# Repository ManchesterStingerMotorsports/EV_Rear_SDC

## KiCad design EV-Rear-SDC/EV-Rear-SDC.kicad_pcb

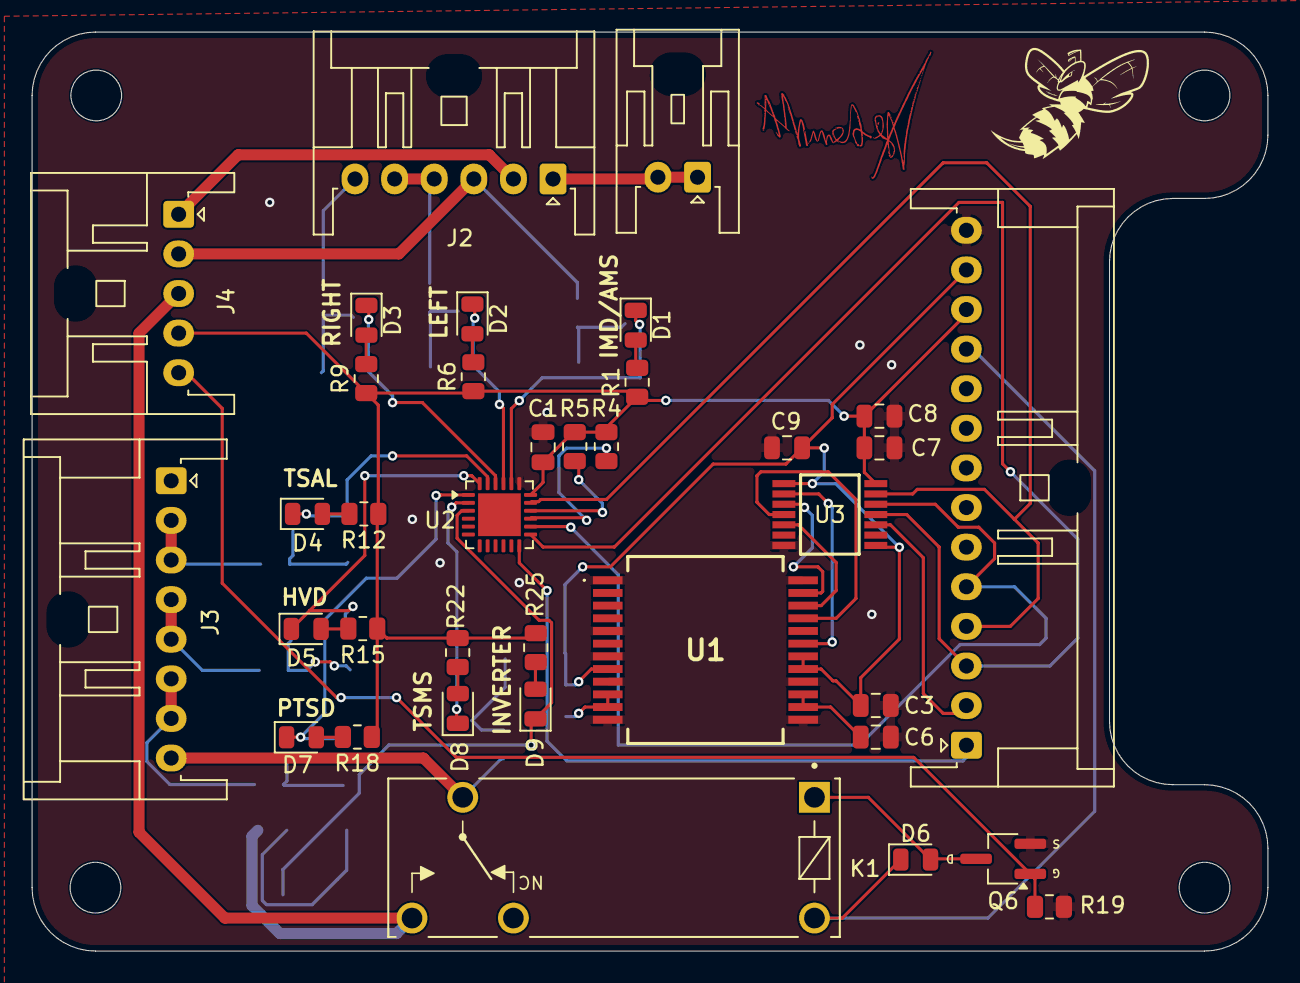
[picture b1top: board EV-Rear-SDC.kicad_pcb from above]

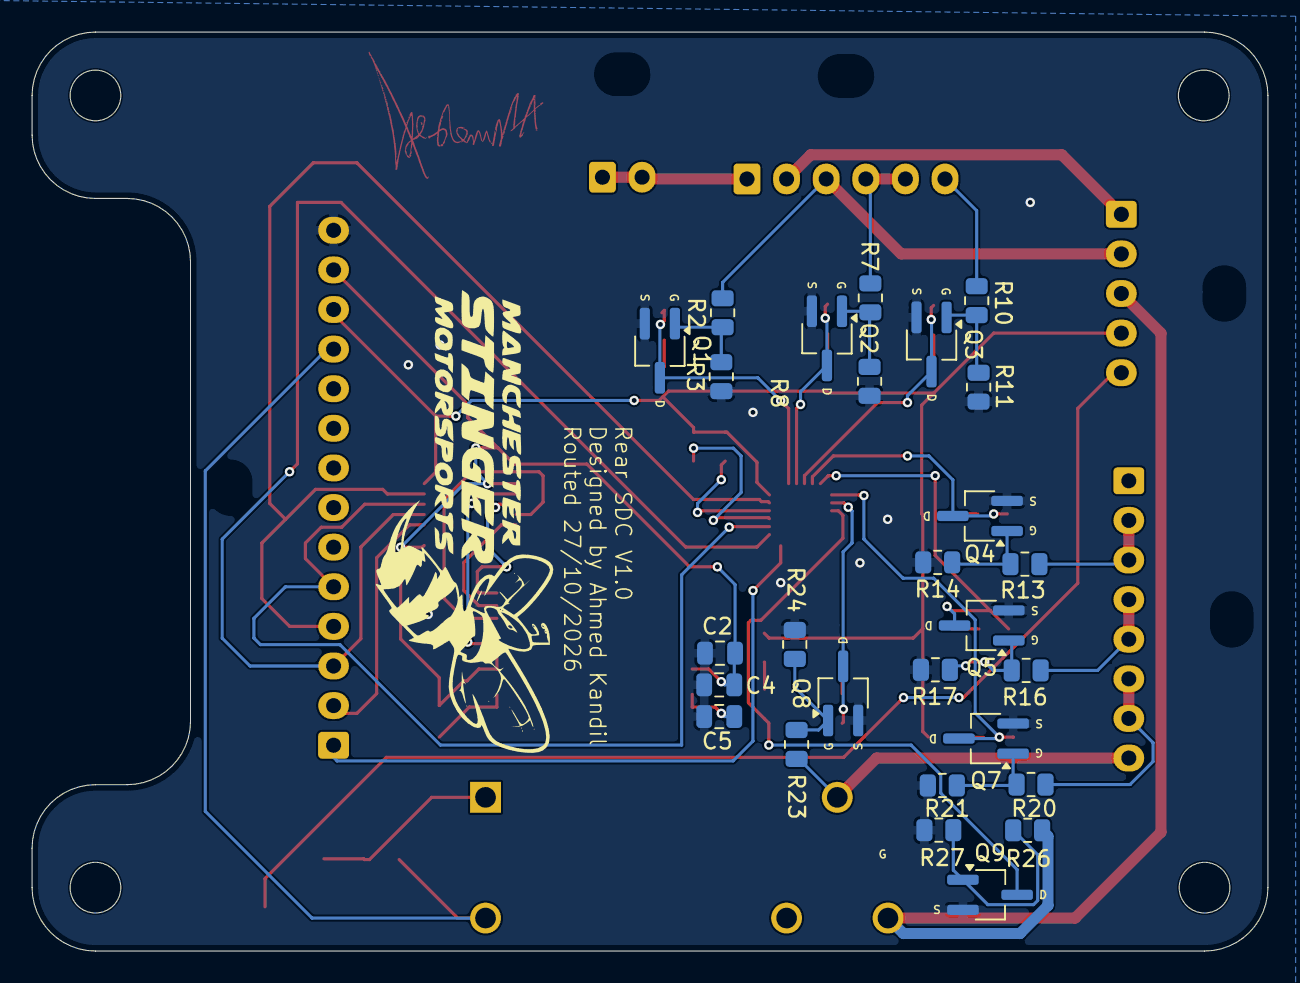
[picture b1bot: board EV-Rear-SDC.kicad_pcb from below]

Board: 2 copper layers, 78.0 x 58.0 mm, 63 parts (27 on the bottom side), 53 nets.

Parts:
C1, C2, C3, C7, C9: 0.1u; C_0805_2012Metric
C4, C6, C8: 1u; C_0805_2012Metric
C5: 10u; C_0805_2012Metric
D1, D2, D3, D4, D5, D7, D8, D9: LED; LED_0805_2012Metric
D6: D; D_0805_2012Metric
J1: JST-XA; JST_XA_S02B-XASK-1_1x02_P2.50mm_Horizontal
J2: Conn_01x06; JST_XA_S06B-XASK-1_1x06_P2.50mm_Horizontal
J3: Conn_01x08; JST_XA_S08B-XASK-1_1x08_P2.50mm_Horizontal
J4: Conn_01x05; JST_XA_S05B-XASK-1_1x05_P2.50mm_Horizontal
J5: Conn_01x14; JST_XA_S14B-XASK-1_1x14_P2.50mm_Horizontal
K1: Relay_SPDT_G6RN
Q1, Q2, Q3, Q4, Q5, Q6, Q7, Q8, Q9: BSS205N; MOSFET_Single_SOT-23
R1, R6, R9, R12, R15, R18, R22, R25: 300R; R_0805_2012Metric
R2, R7, R10, R13, R16, R20, R23, R26: 75K; R_0805_2012Metric
R3, R8, R11, R14, R17, R21, R24, R27: 25k; R_0805_2012Metric
R4, R5: 10k; R_0805_2012Metric
R19: 100k; R_0805_2012Metric
U1: SCH16T-K01-10; SCH16TK0110
U2: QFN-24-1EP_4x4mm_P0.5mm_EP2.7x2.7mm
U3: MAX3390EEUD_T; SOP65P640X110-14N

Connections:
5V_CS_C: J5.1, U2.12 (CS)
5V_CS_D: J5.2, U3.10 (O_VCC4)
5V_MISO: J5.4, U2.17 (SDO), U3.13 (I_VCC1)
5V_MOSI: J5.5, U2.14 (SDI), U3.12 (O_VCC2)
5V_SCLK: J5.3, U2.13 (SCLK), U3.11 (O_VCC3)
+3V3: C2.1, C3.1, C4.1, C9.1, J5.13, U1.8 (V3P3_1), U1.17 (V3P3_2), U1.18 (VDDIO), U3.1 (VL), U3.8 (~THREE-STATE)
+24V: D6.1 (K), J5.11, K1.5
BSPD: J2.2, J4.1
CS_D: U1.22 (CS), U3.5 (I_VL4)
GND: C1.2, C2.2, C3.2, C4.2, C5.2, C6.2, C7.2, C8.2, C9.2, J5.14, Q1.2 (S), Q2.2 (S), Q3.2 (S), Q4.2 (S), Q5.2 (S), Q6.2 (S), Q7.2 (S), Q8.2 (S), Q9.2 (S), R3.1, R8.1, R11.1, R14.1, R17.1, R19.2, R21.1, R24.1, R27.1, U1.1 (HEATSINK_1), U1.5 (RESERVED_1), U1.7 (RESERVED_2), U1.9 (GND_1), U1.12 (GND_2), U1.13 (GND_3), U1.16 (GND_4), U1.24 (HEATSINK_2), U2.19 (GND), U3.7 (GND)
HVD: J3.4, J3.5, R16.2
HVD_S: D5.1 (K), Q5.3 (D), U2.24 (P0.4)
IMD/AMS_IN: J2.3, J4.2, R2.2
IMD/AMS_S: D1.1 (K), Q1.3 (D), U2.20 (P0.0)
Inverter_S: D9.1 (K), Q9.3 (D), U2.3 (P0.7)
Inverter_high: C1.1, C7.1, C8.1, J4.4, J5.12, R1.1, R4.1, R5.1, R6.1, R9.1, R12.1, R15.1, R18.1, R22.1, R25.1, U2.18 (VCC), U3.14 (VCC)
Inverter_low: J4.5, Q6.1 (G), R19.1
L_S: D2.1 (K), Q2.3 (D), U2.21 (P0.1)
Left: J2.4, J2.5, R7.2
MISO: U1.19 (MISO), U3.2 (O_VL1)
MOSI: U1.23 (MOSI), U3.3 (I_VL2)
unnamed: D1.2 (A), R1.2
unnamed: D2.2 (A), R6.2
unnamed: D3.2 (A), R9.2
unnamed: D4.2 (A), R12.2
unnamed: D5.2 (A), R15.2
unnamed: D6.2 (A), K1.1, Q6.3 (D)
unnamed: D7.2 (A), R18.2
unnamed: D8.2 (A), R22.2
unnamed: D9.2 (A), R25.2
unnamed: J1.1, J1.2, J2.1
unnamed: Q1.1 (G), R2.1, R3.2
unnamed: Q2.1 (G), R7.1, R8.2
unnamed: Q3.1 (G), R10.1, R11.2
unnamed: Q4.1 (G), R13.1, R14.2
unnamed: Q5.1 (G), R16.1, R17.2
unnamed: Q7.1 (G), R20.1, R21.2
unnamed: Q8.1 (G), R23.1, R24.2
unnamed: Q9.1 (G), R26.1, R27.2
unnamed: C5.1, U1.10 (VREGA2), U1.11 (VREGA)
unnamed: C6.1, U1.14 (VREGD2), U1.15 (VREGD)
unnamed: R5.2, U2.16 (INT)
unnamed: R4.2, U2.15 (RESET)
PTSDIL_S: D7.1 (K), Q7.3 (D), U2.1 (P0.5)
PTSD_IL: J3.6, J3.7, R20.2
R_S: D3.1 (K), Q3.3 (D), U2.22 (P0.2)
Relay_out: J4.3, K1.3, R26.2
Right(Out): J2.6, R10.2
SCLK: U1.21 (SCK), U3.4 (I_VL3)
TSAL: J3.2, J3.3, R13.2
TSAL_S: D4.1 (K), Q4.3 (D), U2.23 (P0.3)
TSMS: J3.8, K1.2, R23.2
TSMS_S: D8.1 (K), Q8.3 (D), U2.2 (P0.6)
